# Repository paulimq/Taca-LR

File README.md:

# Proyecto taca-taca
## Requerimientos:

- [x] Armar estructura a medida para el taca
- [x] Instalar sistema de luces LED en la estructura
- [x] Diseñar un sistema basado en displays 7 segmentos
- [ ] Diseño de placa PCB
- [ ] Programación para contador de goles
- [ ] Montar botones y cableado
- [ ] Definir sistema de alimentación e instalarlo

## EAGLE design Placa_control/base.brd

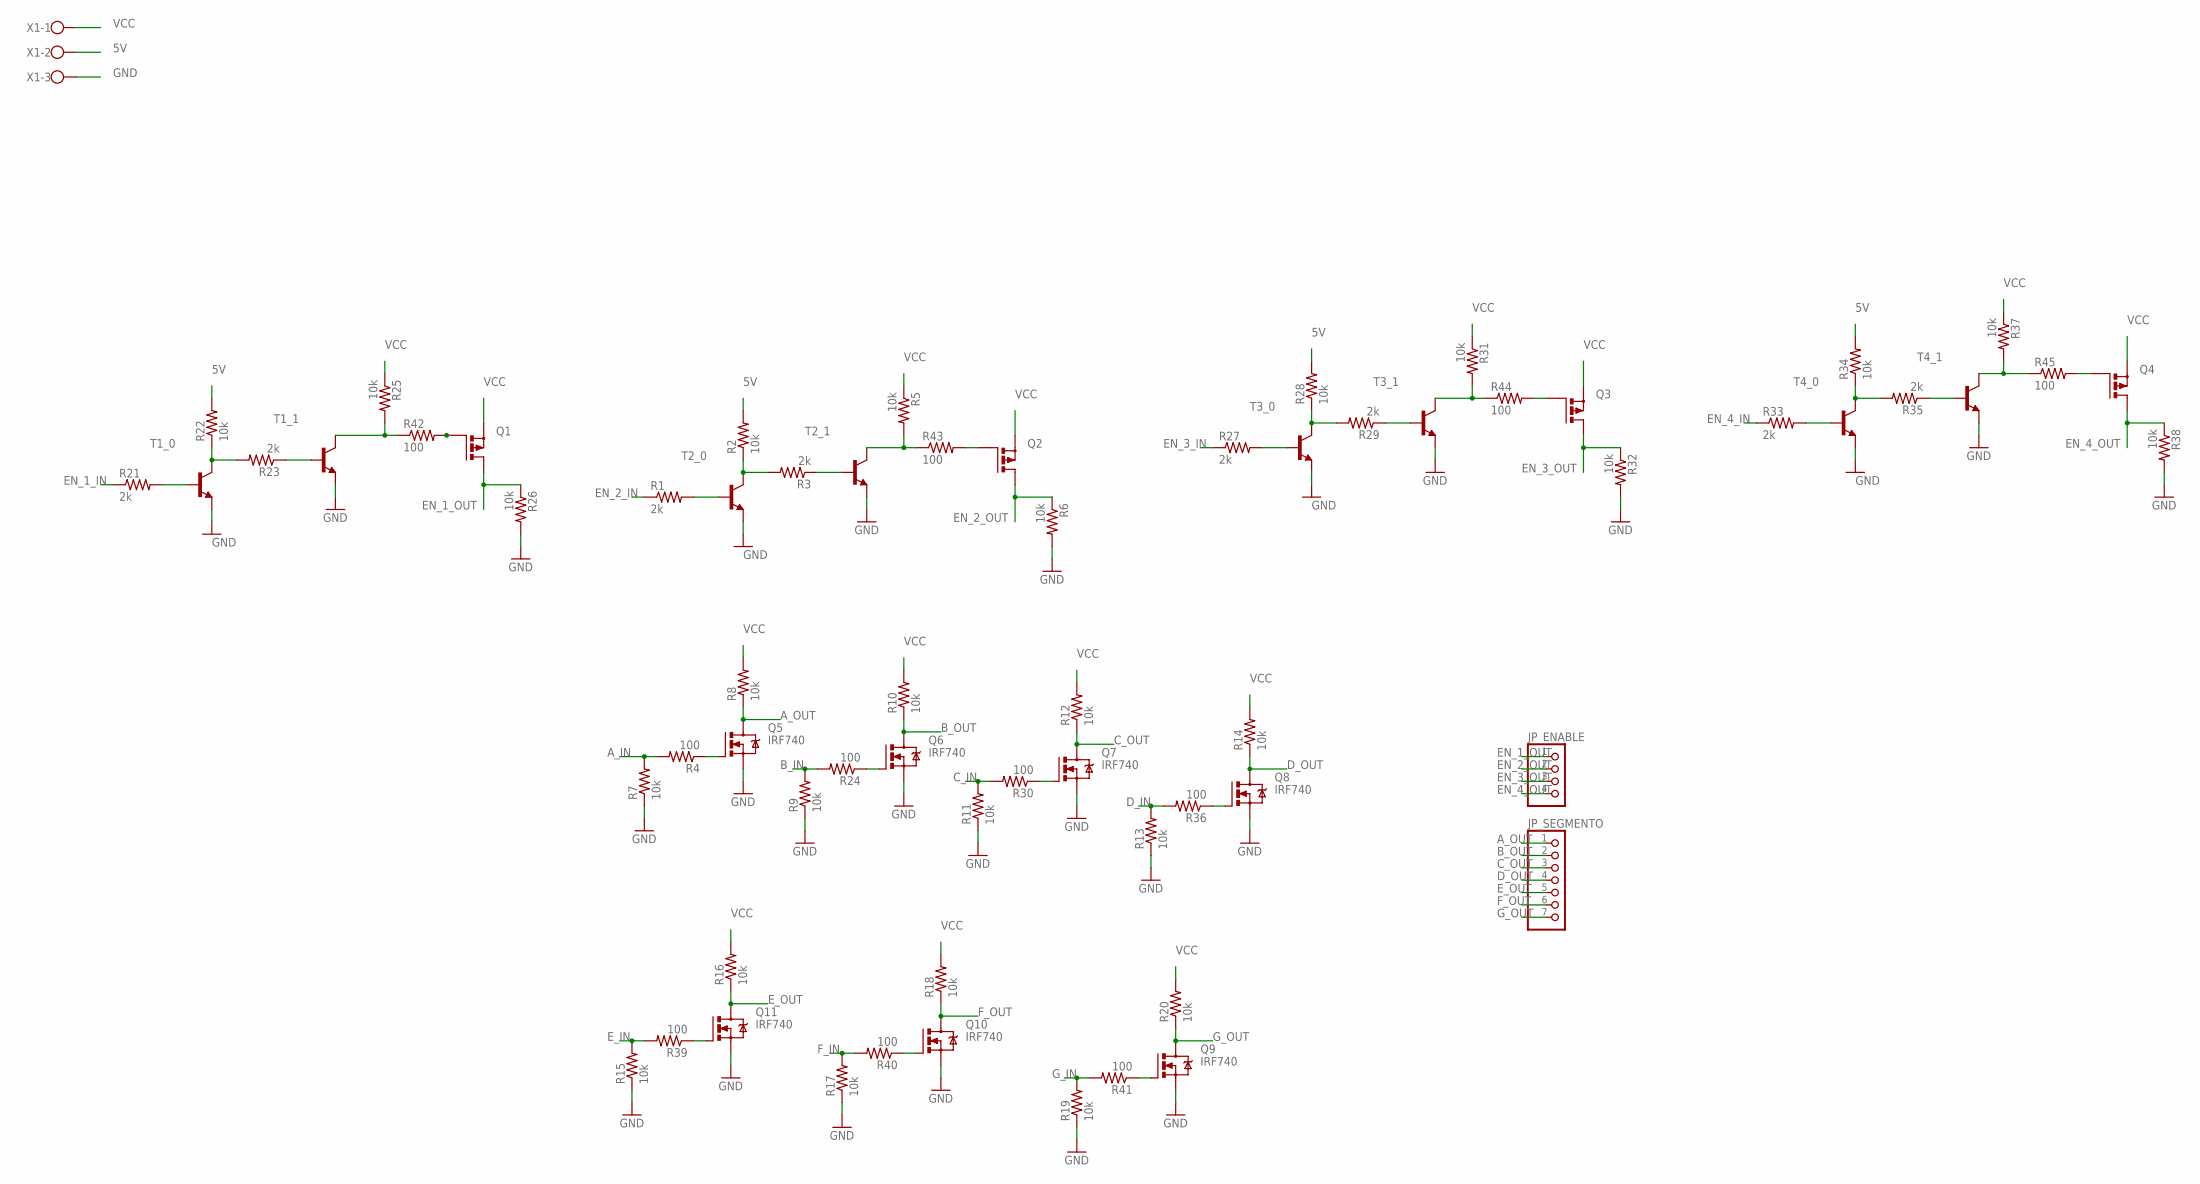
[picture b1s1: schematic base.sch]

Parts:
JP_ENABLE: PINHD-1X4; 1X04
JP_SEGMENTO: PINHD-1X7; 1X07
Q1, Q2, Q3, Q4: PMOSFET_PTO220BV; TO220BV
Q5, Q6, Q7, Q8, Q9, Q10, Q11: IRF740; TO220BV
R1, R3, R21, R23, R27, R29, R33, R35: 2k; 0207/10
R2, R5, R6, R7, R8, R9, R10, R11, R12, R13, R14, R15, R16, R17, R18, R19, R20, R22, R25, R26, R28, R31, R32, R34, R37, R38: 10k; 0207/10
R4, R24, R30, R36, R39, R40, R41, R42, R43, R44, R45: 100; 0207/10
T1_0, T1_1, T2_0, T2_1, T3_0, T3_1, T4_0, T4_1: 2N2222-NPN-TO92-EBC; TO92-EBC
X1: W237-103

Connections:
5V: R2.2, R22.2, R28.2, R34.2, X1.2
A_IN: R4.2, R7.2
A_OUT: JP_SEGMENTO.1, Q5.D, R8.1
B_IN: R9.2, R24.2
B_OUT: JP_SEGMENTO.2, Q6.D, R10.1
C_IN: R11.2, R30.2
C_OUT: JP_SEGMENTO.3, Q7.D, R12.1
D_IN: R13.2, R36.2
D_OUT: JP_SEGMENTO.4, Q8.D, R14.1
EN_1_IN: R21.1
EN_1_OUT: JP_ENABLE.1, Q1.D, R26.1
EN_2_IN: R1.1
EN_2_OUT: JP_ENABLE.2, Q2.D, R6.1
EN_3_IN: R27.1
EN_3_OUT: JP_ENABLE.3, Q3.D, R32.1
EN_4_IN: R33.1
EN_4_OUT: JP_ENABLE.4, Q4.D, R38.1
E_IN: R15.2, R39.2
E_OUT: JP_SEGMENTO.5, Q11.D, R16.1
F_IN: R17.2, R40.2
F_OUT: JP_SEGMENTO.6, Q10.D, R18.1
GND: Q5.S, Q6.S, Q7.S, Q8.S, Q9.S, Q10.S, Q11.S, R6.2, R7.1, R9.1, R11.1, R13.1, R15.1, R17.1, R19.1, R26.2, R32.2, R38.2, T1_0.E, T1_1.E, T2_0.E, T2_1.E, T3_0.E, T3_1.E, T4_0.E, T4_1.E, X1.3
G_IN: R19.2, R41.2
G_OUT: JP_SEGMENTO.7, Q9.D, R20.1
unnamed: R1.2, T2_0.B
unnamed: R2.1, R3.2, T2_0.C
unnamed: R3.1, T2_1.B
unnamed: R5.2, R43.1, T2_1.C
unnamed: Q5.G, R4.1
unnamed: Q6.G, R24.1
unnamed: Q7.G, R30.1
unnamed: Q8.G, R36.1
unnamed: Q1.G, R42.2
unnamed: Q10.G, R40.1
unnamed: Q9.G, R41.1
unnamed: Q2.G, R43.2
unnamed: Q3.G, R44.2
unnamed: Q4.G, R45.2
unnamed: Q11.G, R39.1
unnamed: R21.2, T1_0.B
unnamed: R22.1, R23.2, T1_0.C
unnamed: R23.1, T1_1.B
unnamed: R25.2, R42.1, T1_1.C
unnamed: R27.2, T3_0.B
unnamed: R28.1, R29.2, T3_0.C
unnamed: R29.1, T3_1.B
unnamed: R31.2, R44.1, T3_1.C
unnamed: R33.2, T4_0.B
unnamed: R34.1, R35.2, T4_0.C
unnamed: R35.1, T4_1.B
unnamed: R37.2, R45.1, T4_1.C
VCC: Q1.S, Q2.S, Q3.S, Q4.S, R5.1, R8.2, R10.2, R12.2, R14.2, R16.2, R18.2, R20.2, R25.1, R31.1, R37.1, X1.1

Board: 2 copper layers, 67 parts (0 on the bottom side), 48 nets, no tracks yet.

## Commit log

2019-06-14 INIT
2019-09-12 Avance placa
2019-09-12 Git Ignore
